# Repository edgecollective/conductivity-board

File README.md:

# conductivity-board

- [Conceptual diagram](ref_docs/conductivityCircuit.pdf)
- [Schematic](conductive.pdf)

## Contributors

(Listed alphabetically)

- Don Blair
- Brian Mayton
- Laura Perovich
- Yagiz Sutcu
- Craig Versek

## Notes / Todo

- The rail splitter chip library (and thus the schematic)  incorrectly uses '74H4051' instead of '74HC4051' as the name of the chip.  This needs to be modified at the library level, then updated in the schematic.

## Parts

- [74HC4051D](https://www.digikey.com/product-detail/en/935298447118/1727-1032-1-ND/3749039?curr=usd&WT.z_cid=ref_octopart_dkc_buynow&site=us) (Multiplexer)

- [AD8531](https://www.digikey.com/product-detail/en/AD8531ARZ-REEL/AD8531ARZ-REELCT-ND/3647792?curr=usd&WT.z_cid=ref_octopart_dkc_buynow&site=us) (Single op-amp)

- [AD8534](https://www.digikey.com/product-detail/en/AD8534ARZ/AD8534ARZ-ND/621279?curr=usd&WT.z_cid=ref_octopart_dkc_buynow&site=us) (Quad op-amp)

- [TLE2426](http://www.mouser.com/ProductDetail/Texas-Instruments/TLE2426IDR/?qs=sGAEpiMZZMuBck1X%252b7j9fO4UAZmXrrVcv6AkpUgzMyc%3d) (Rail splitter)

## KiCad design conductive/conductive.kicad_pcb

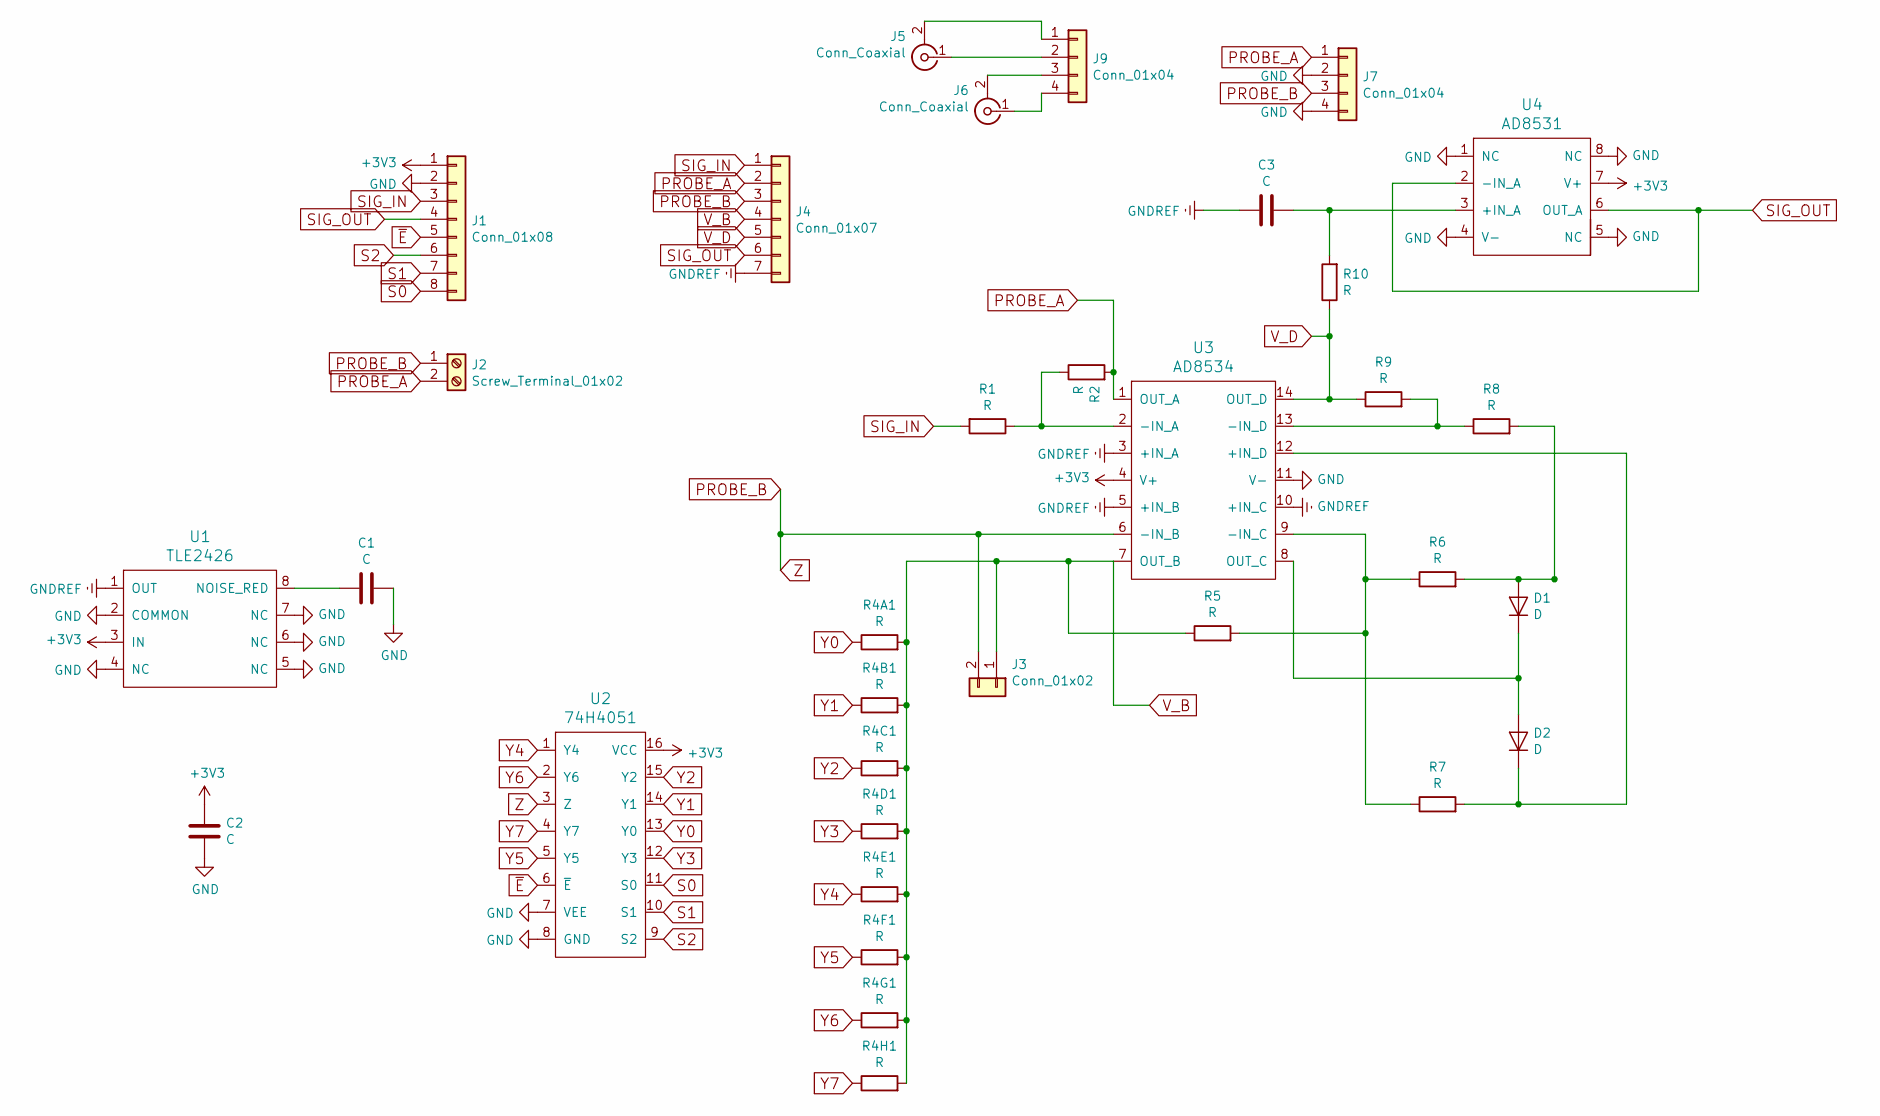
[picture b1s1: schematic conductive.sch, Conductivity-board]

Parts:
C1, C2, C3: C; C_0805
D1, D2: D; D_1206
J1: Conn_01x08; Pin_Header_Straight_1x08_Pitch2.54mm
J2: Screw_Terminal_01x02; TerminalBlock_4UCON_19963_02x3.5mm_Straight
J3: Conn_01x02; Pin_Header_Straight_1x02_Pitch2.54mm
J4: Conn_01x07; Pin_Header_Straight_1x07_Pitch2.54mm
J5, J6: Conn_Coaxial; SMA_SMD_Jack_Straight
J7, J9: Conn_01x04; Pin_Header_Straight_1x04_Pitch2.54mm
R1, R2, R4A1, R4B1, R4C1, R4D1, R4E1, R4F1, R4G1, R4H1, R5, R6, R7, R8, R9, R10: R; R_0805
U1: TLE2426; SOIC-8-N
U2: 74H4051; SO-16-N
U3: AD8534; SOIC-14_N
U4: AD8531; SOIC-8-N

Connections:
+3V3: C2.2, J1.1, U1.3 (IN), U2.16 (VCC), U3.4 (V+), U4.7 (V+)
GND: C1.1, C2.1, J1.2, J7.2, J7.4, U1.2 (COMMON), U1.4 (NC), U1.5 (NC), U1.6 (NC), U1.7 (NC), U2.7 (VEE), U2.8 (GND), U3.11 (V-), U4.1 (NC), U4.4 (V-), U4.5 (NC), U4.8 (NC)
GNDREF: C3.2, J4.7, U1.1 (OUT), U3.3 (+IN_A), U3.5 (+IN_B), U3.10 (+IN_C)
unnamed: C1.2, U1.8 (NOISE_RED)
unnamed: C3.1, R10.2, U4.3 (+IN_A)
unnamed: D1.1 (K), D2.2 (A), U3.8 (OUT_C)
unnamed: D1.2 (A), R6.2, R8.2
unnamed: D2.1 (K), R7.2, U3.12 (+IN_D)
unnamed: J5.1 (In), J9.2
unnamed: J5.2 (Ext), J9.1
unnamed: J6.1 (In), J9.4
unnamed: J6.2 (Ext), J9.3
unnamed: R1.1, R2.1, U3.2 (-IN_A)
unnamed: R5.2, R6.1, R7.1, U3.9 (-IN_C)
unnamed: R8.1, R9.2, U3.13 (-IN_D)
PROBE_A: J2.2, J4.2, J7.1, R2.2, U3.1 (OUT_A)
PROBE_B: J2.1, J3.2, J4.3, J7.3, U2.3 (Z), U3.6 (-IN_B)
S0: J1.8, U2.11 (S0)
S1: J1.7, U2.10 (S1)
S2: J1.6, U2.9 (S2)
SIG_IN: J1.3, J4.1, R1.2
SIG_OUT: J1.4, J4.6, U4.2 (-IN_A), U4.6 (OUT_A)
V_B: J3.1, J4.4, R4A1.2, R4B1.2, R4C1.2, R4D1.2, R4E1.2, R4F1.2, R4G1.2, R4H1.2, R5.1, U3.7 (OUT_B)
V_D: J4.5, R9.1, R10.1, U3.14 (OUT_D)
Y0: R4A1.1, U2.13 (Y0)
Y1: R4B1.1, U2.14 (Y1)
Y2: R4C1.1, U2.15 (Y2)
Y3: R4D1.1, U2.12 (Y3)
Y4: R4E1.1, U2.1 (Y4)
Y5: R4F1.1, U2.5 (Y5)
Y6: R4G1.1, U2.2 (Y6)
Y7: R4H1.1, U2.4 (Y7)
~E: J1.5, U2.6 (~E)

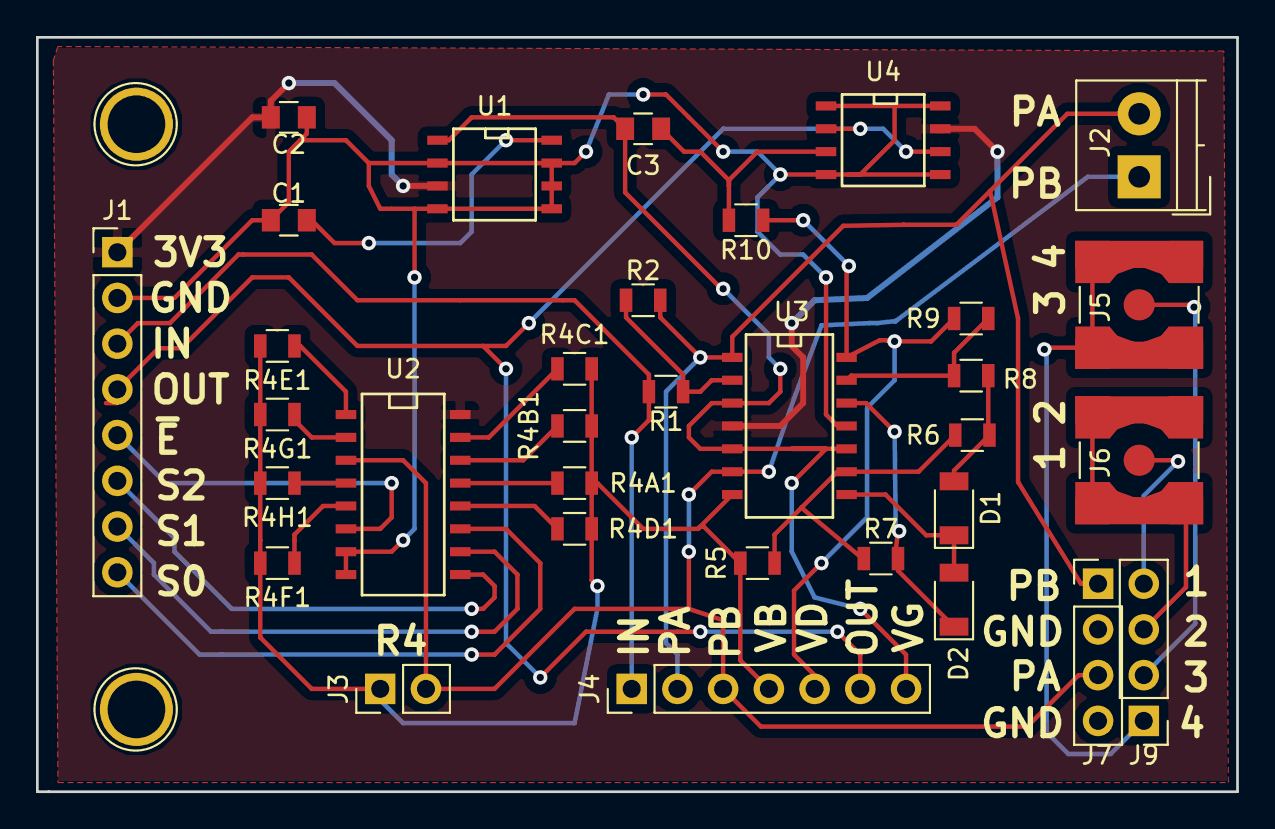
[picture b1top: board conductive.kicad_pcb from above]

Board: 2 copper layers, 66.7 x 41.9 mm, 33 parts (0 on the bottom side), 33 nets.
